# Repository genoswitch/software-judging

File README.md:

# software
toehold switch software

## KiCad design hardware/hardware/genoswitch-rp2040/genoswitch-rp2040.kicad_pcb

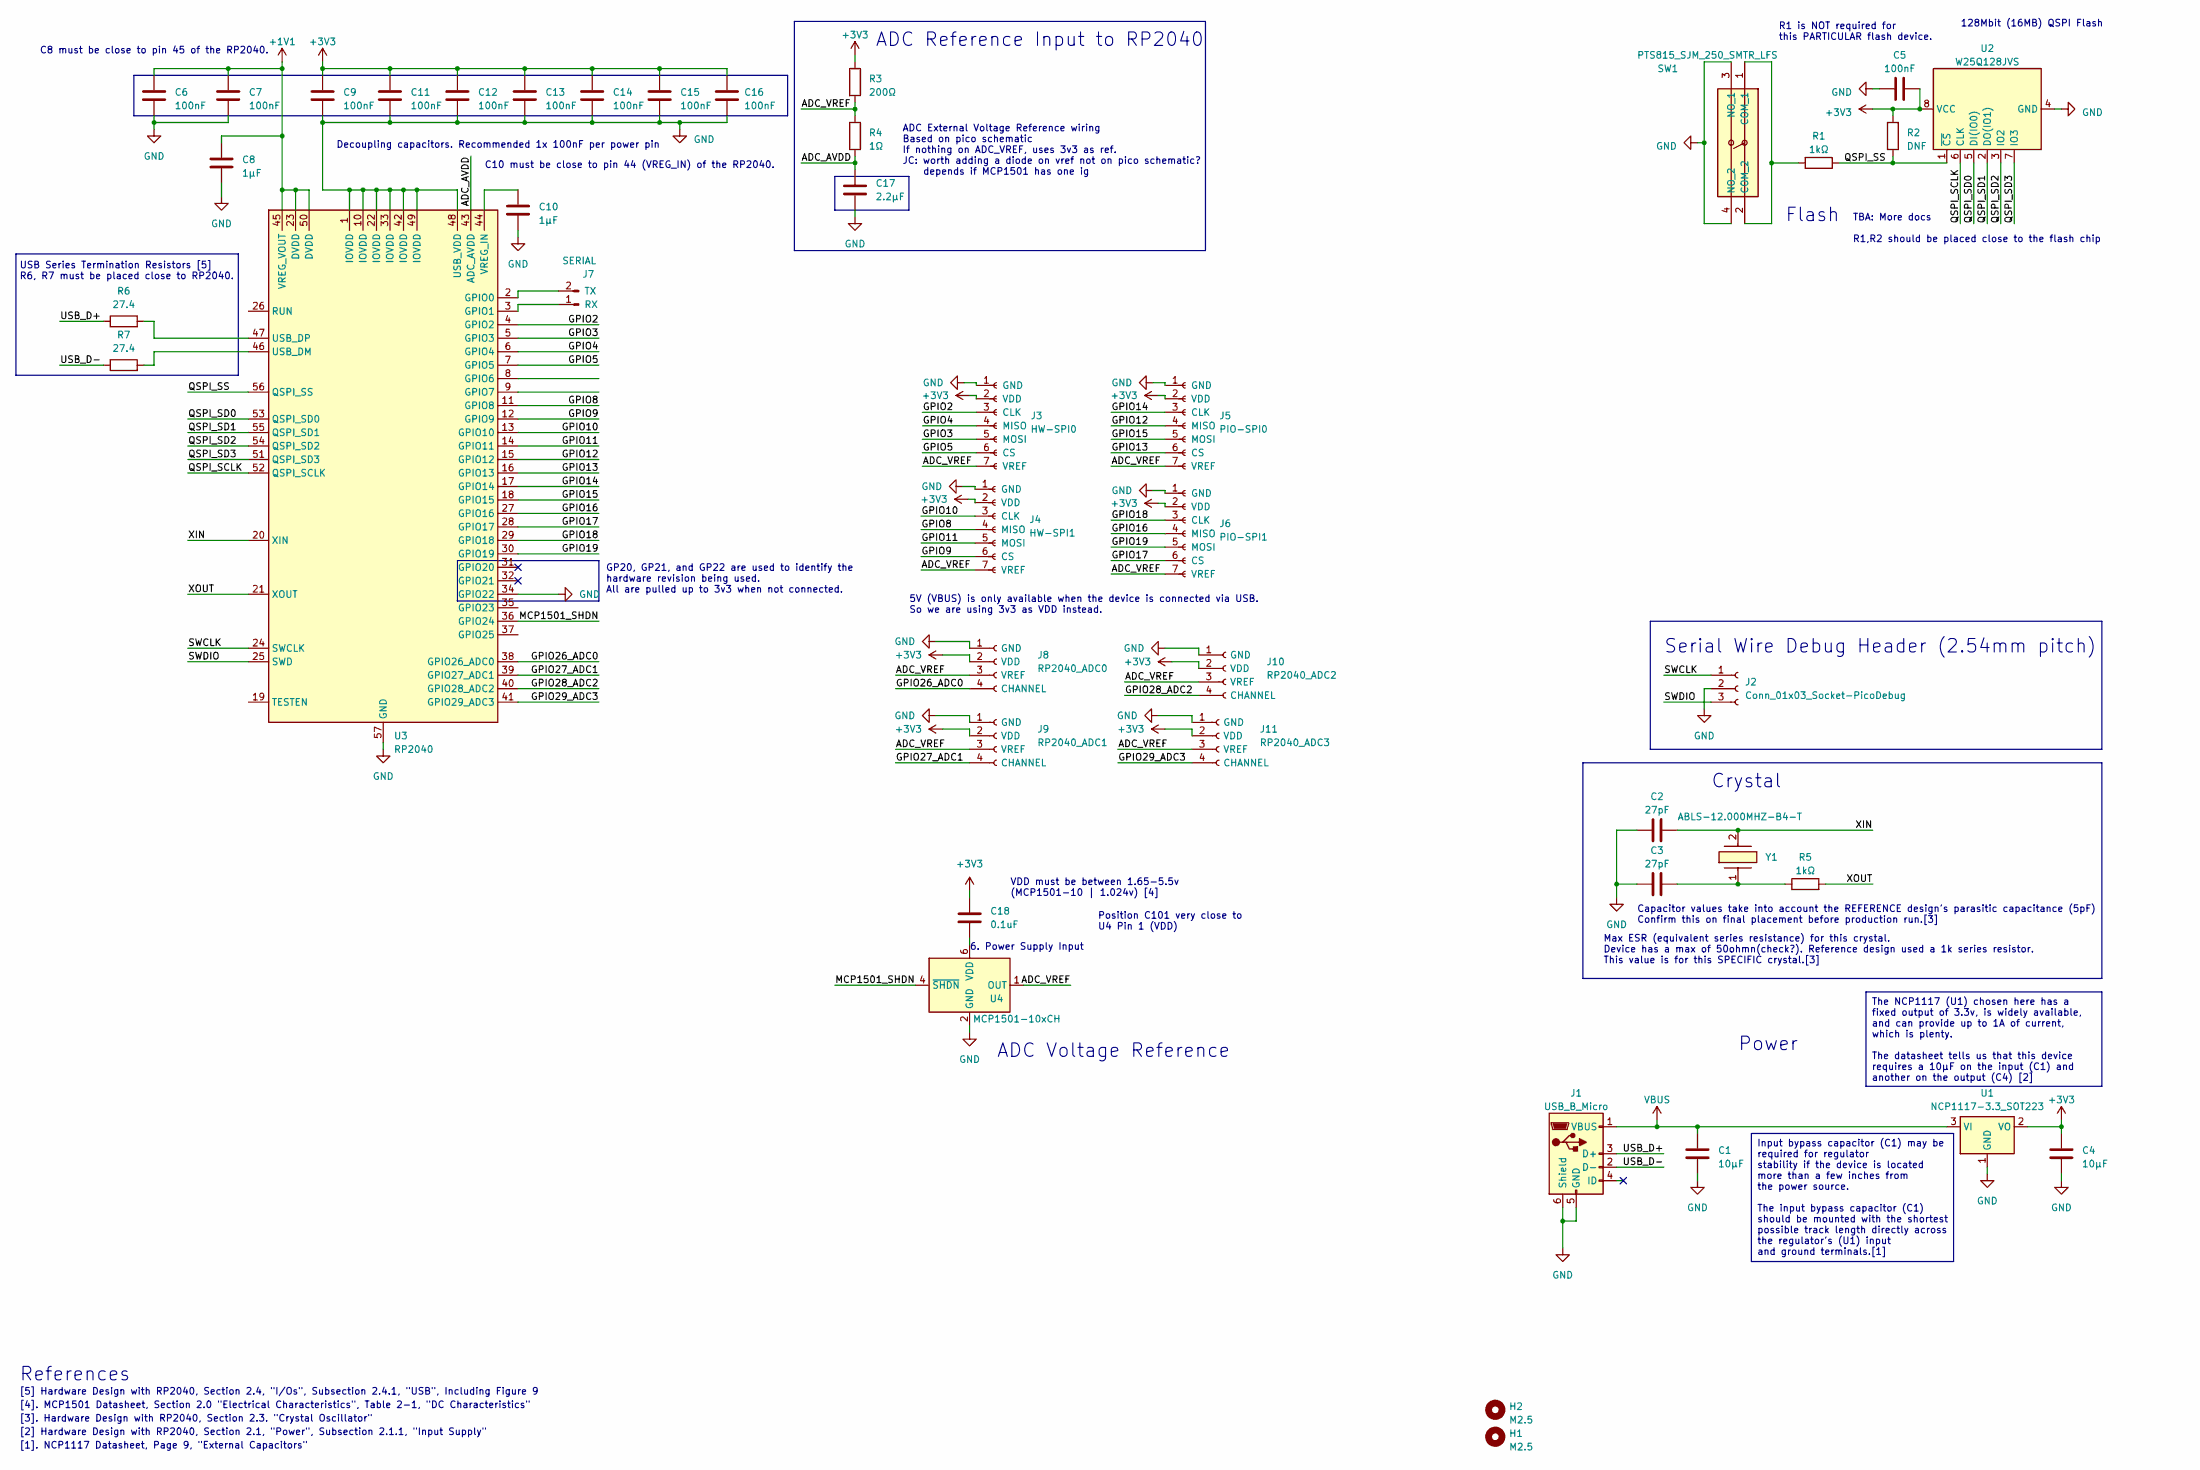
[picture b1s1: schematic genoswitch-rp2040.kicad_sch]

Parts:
C1, C4: 10μF; C_0201_0603Metric
C2, C3: 27pF; C_0201_0603Metric
C5, C6, C7, C9, C11, C12, C13, C14, C15, C16: 100nF; C_0201_0603Metric
C8, C10: 1μF; C_0201_0603Metric
C17: 2.2μF; C_0201_0603Metric
C18: 0.1uF; C_0201_0603Metric
H1, H2: M2.5; MountingHole_2.7mm_M2.5_Pad_TopBottom
J1: USB_B_Micro; USB_Micro-B_Amphenol_10118193-0001LF_Horizontal
J2: Conn_01x03_Socket-PicoDebug; PinHeader_1x03_P2.54mm_Vertical
J3: HW-SPI0; JST_PH_S7B-PH-K_1x07_P2.00mm_Horizontal
J4: HW-SPI1; JST_PH_S7B-PH-K_1x07_P2.00mm_Horizontal
J5: PIO-SPI0; JST_PH_S7B-PH-K_1x07_P2.00mm_Horizontal
J6: PIO-SPI1; JST_PH_S7B-PH-K_1x07_P2.00mm_Horizontal
J7: SERIAL; PinHeader_1x02_P2.54mm_Vertical
J8: RP2040_ADC0; JST_PH_S4B-PH-K_1x04_P2.00mm_Horizontal
J9: RP2040_ADC1; JST_PH_S4B-PH-K_1x04_P2.00mm_Horizontal
J10: RP2040_ADC2; JST_PH_S4B-PH-K_1x04_P2.00mm_Horizontal
J11: RP2040_ADC3; JST_PH_S4B-PH-K_1x04_P2.00mm_Horizontal
R1, R5: 1kΩ; R_0201_0603Metric
R2: DNF; R_0201_0603Metric
R3: 200Ω; R_0201_0603Metric
R4: 1Ω; R_0201_0603Metric
R6, R7: 27.4; R_0201_0603Metric
SW1: PTS815_SJM_250_SMTR_LFS; PTS815SJM250SMTRLFS; Mouser Part Number 611-PTS815SJM250SMTR
U1: NCP1117-3.3_SOT223; SOT-223-3_TabPin2
U2: W25Q128JVS; SOIC-8_5.23x5.23mm_P1.27mm
U3: RP2040; QFN-56-1EP_7x7mm_P0.4mm_EP3.2x3.2mm
U4: MCP1501-10xCH; SOT-23-6
Y1: ABLS-12.000MHZ-B4-T; ABLS; Mouser Part Number 815-ABLS-12.0M-T

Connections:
+1V1: C6.1, C7.1, C8.1, U3.23 (DVDD), U3.45 (VREG_VOUT), U3.50 (DVDD)
+3V3: C4.1, C5.2, C9.1, C11.1, C12.1, C13.1, C14.1, C15.1, C16.1, C18.2, J3.2 (VDD), J4.2 (VDD), J5.2 (VDD), J6.2 (VDD), J8.2 (VDD), J9.2 (VDD), J10.2 (VDD), J11.2 (VDD), R2.2, R3.1, U1.2 (VO), U2.8 (VCC)
/ADC_AVDD: C17.1, R4.2, U3.43 (ADC_AVDD)
/ADC_VREF: J3.7 (VREF), J4.7 (VREF), J5.7 (VREF), J6.7 (VREF), J8.3 (VREF), J9.3 (VREF), J10.3 (VREF), J11.3 (VREF), R3.2, R4.1, U4.1 (OUT)
/GPIO4: J3.4 (DOUT), U3.6 (GPIO4)
/GPIO5: J3.6 (CS), U3.7 (GPIO5)
/GPIO6: J3.3 (CLK), U3.4 (GPIO2), U3.8 (GPIO6)
/GPIO7: J3.5 (DIN), U3.5 (GPIO3), U3.9 (GPIO7)
/GPIO8: J4.4 (DOUT), U3.11 (GPIO8)
/GPIO9: J4.6 (CS), U3.12 (GPIO9)
/GPIO10: J4.3 (CLK), U3.13 (GPIO10)
/GPIO11: J4.5 (DIN), U3.14 (GPIO11)
/GPIO12: J5.4 (DOUT), U3.15 (GPIO12)
/GPIO13: J5.6 (CS), U3.16 (GPIO13)
/GPIO14: J5.3 (CLK), U3.17 (GPIO14)
/GPIO15: J5.5 (DIN), U3.18 (GPIO15)
/GPIO16: J6.4 (DOUT), U3.27 (GPIO16)
/GPIO17: J6.6 (CS), U3.28 (GPIO17)
/GPIO18: J6.3 (CLK), U3.29 (GPIO18)
/GPIO19: J6.5 (DIN), U3.30 (GPIO19)
/GPIO26_ADC0: J8.4 (CHANNEL), U3.38 (GPIO26_ADC0)
/GPIO27_ADC1: J9.4 (CHANNEL), U3.39 (GPIO27_ADC1)
/GPIO28_ADC2: J10.4 (CHANNEL), U3.40 (GPIO28_ADC2)
/GPIO29_ADC3: J11.4 (CHANNEL), U3.41 (GPIO29_ADC3)
/MCP1501_SHDN: U3.36 (GPIO24), U4.4 (~SHDN)
/QSPI_SCLK: U2.6 (CLK), U3.52 (QSPI_SCLK)
/QSPI_SD0: U2.5 (DI(IO0)), U3.53 (QSPI_SD0)
/QSPI_SD1: U2.2 (DO(IO1)), U3.55 (QSPI_SD1)
/QSPI_SD2: U2.3 (IO2), U3.54 (QSPI_SD2)
/QSPI_SD3: U2.7 (IO3), U3.51 (QSPI_SD3)
/QSPI_SS: R1.1, R2.1, U2.1 (~CS), U3.56 (QSPI_SS)
/SWCLK: J2.1, U3.24 (SWCLK)
/SWDIO: J2.3, U3.25 (SWD)
/USB_D+: J1.3 (D+), R6.1
/USB_D-: J1.2 (D-), R7.1
/XIN: C2.2, U3.20 (XIN), Y1.2
/XOUT: R5.2, U3.21 (XOUT)
GND: C1.2, C2.1, C3.1, C4.2, C5.1, C6.2, C7.2, C8.2, C9.2, C10.2, C11.2, C12.2, C13.2, C14.2, C15.2, C16.2, C17.2, J1.5 (GND), J1.6 (Shield), J2.2, J3.1 (GND), J4.1 (GND), J5.1 (GND), J6.1 (GND), J8.1 (GND), J9.1 (GND), J10.1 (GND), J11.1 (GND), SW1.3 (NO_1), SW1.4 (NO_2), U1.1 (GND), U2.4 (GND), U3.1 (IOVDD), U3.10 (IOVDD), U3.22 (IOVDD), U3.33 (IOVDD), U3.34 (GPIO22), U3.42 (IOVDD), U3.48 (USB_VDD), U3.49 (IOVDD), U3.57 (GND), U4.2 (GND), U4.3 (GND), U4.5 (GND)
unnamed: C3.2, R5.1, Y1.1
unnamed: J7.1 (RX), U3.3 (GPIO1)
unnamed: J7.2 (TX), U3.2 (GPIO0)
unnamed: R1.2, SW1.1 (COM_1), SW1.2 (COM_2)
unnamed: R7.2, U3.46 (USB_DM)
unnamed: R6.2, U3.47 (USB_DP)
unnamed: C10.1, U3.44 (VREG_IN)
unnamed: C18.1, U4.6 (VDD)
VBUS: C1.1, J1.1 (VBUS), U1.3 (VI)

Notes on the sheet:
The NCP1117 (U1) chosen here has a fixed output of 3.3v, is widely available, and can provide up to 1A of current, which is plenty. The datasheet tells us that this device requires a 10μF on the input (C1) and another on the output (C4) [2]
Input bypass capacitor (C1) may be required for regulator stability if the device is located more than a few inches from the power source. The input bypass capacitor (C1) should be mounted with the shortest possible track length directly across the regulator's (U1) input and ground terminals.[1]
VDD must be between 1.65-5.5v (MCP1501-10 | 1.024v) [4]
6. Power Supply Input
5V (VBUS) is only available when the device is connected via USB. So we are using 3v3 as VDD instead.
[4]. MCP1501 Datasheet, Section 2.0 "Electrical Characteristics", Table 2-1, "DC Characteristics"
Position C101 very close to U4 Pin 1 (VDD)
[5] Hardware Design with RP2040, Section 2.4, "I/Os", Subsection 2.4.1, "USB", Including Figure 9
128Mbit (16MB) QSPI Flash
USB Series Termination Resistors [5] R6, R7 must be placed close to RP2040.
[3]. Hardware Design with RP2040, Section 2.3. "Crystal Oscillator"
Decoupling capacitors. Recommended 1x 100nF per power pin
GP20, GP21, and GP22 are used to identify the hardware revision being used. All are pulled up to 3v3 when not connected.
Power
Serial Wire Debug Header (2.54mm pitch)
Crystal
R1 is NOT required for this PARTICULAR flash device.
[1]. NCP1117 Datasheet, Page 9, "External Capacitors"
ADC Voltage Reference
C10 must be close to pin 44 (VREG_IN) of the RP2040.
ADC External Voltage Reference wiring Based on pico schematic If nothing on ADC_VREF, uses 3v3 as ref. JC: worth adding a diode on vref not on pico schematic? depends if MCP1501 has one ig
TBA: More docs R1,R2 should be placed close to the flash chip
C8 must be close to pin 45 of the RP2040.
ADC Reference Input to RP2040
Capacitor values take into account the REFERENCE design's parasitic capacitance (5pF) Confirm this on final placement before production run.[3]
Max ESR (equivalent series resistance) for this crystal. Device has a max of 50ohmn(check?). Reference design used a 1k series resistor. This value is for this SPECIFIC crystal.[3]
Flash
[2] Hardware Design with RP2040, Section 2.1, "Power", Subsection 2.1.1, "Input Supply"
References

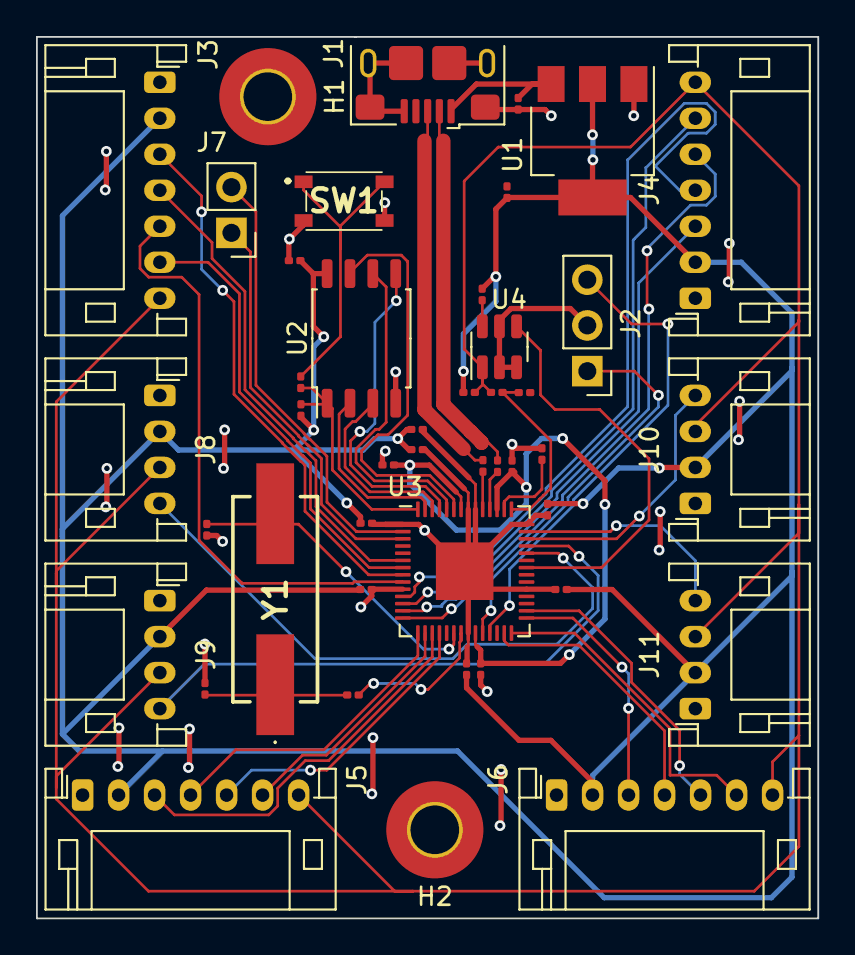
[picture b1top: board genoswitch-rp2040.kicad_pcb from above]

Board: 2 copper layers, 43.4 x 49.0 mm, 44 parts (0 on the bottom side), 47 nets.

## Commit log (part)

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2023-01-25 (lib) Add pico-sdk submodule
2023-01-25 add build/ folders to gitignore
2023-01-25 Fetch FreeRTOS import script from kernel repo
2023-01-28 (ide): Set CMake build and src directories
2023-01-28 (ide): Add picoprobe debug configuration
2023-01-28 Include FreeRTOS (and config dir); link Kernel and Kernel-Heap4
2023-01-28 Add comments, move prototypes to .h file
2023-01-28 Add cortex debug files, comments to gitignore
2023-01-28 Add tinyusb config files from webusb_serial demo (unmodified)
2023-01-29 Initial TinyUSB WebUSB support (enumerates successfully)
    Code based on the TinyUSB WebUSB_Serial demo, but we are still using FreeRTOS.
    FreeRTOS code inspired from cdc freertos examples from TinyUSB.
2023-02-17 Add cmake-git-version-tracking submodule
2023-02-18 Display hw/fw information over stdout on boot
2023-03-11 PoC queue based messaging between tasks
2023-03-12 (tasks/mcu_temp): Send temp data over usb, optionally over stdout configurable by #define
2023-03-23 (cmake): Move main cmake calls to own file
    This is so that we can split the flashloader and main program into different cmake files.
2023-03-23 (cmake): Add module path var and linker script helper
2023-03-23 (cmake/main): Create subproject name var
2023-03-23 (cmake): Set project variable
2023-03-23 (cmake): Include new cmake scripts in build
2023-03-24 (cmake): Update linker helper for new linker files
2023-03-24 (cmake): PoC new way of combining binaries
    This method is based off of picowota (https://github.com/usedbytes/picowota) as well as the pico sdk itself.
    With this method we can create all of the expected output files (.elf, .hex, .uf2) as well as register it as an executable in cmake.
    This commit is just a proof of concept, in later commits this will be extended to have the functionality described above.
2023-03-25 (linker): pico-flashloader requires application to have boot2
    Unlike picowota, pico-flashloader uses boot2 to identify the start of image. If space is a concern we could change this behaviour to use a magic string like picowota instead.
2023-04-06 (cmake/flashloader): Only make bin output
2023-04-06 (cmake/combined): Generate a combined uf2
2023-04-06 (combined/cmake): Add comments for custom commands
2023-04-09 (linker): Move flashloader ld files to own dir
2023-04-09 (linker): Add flashloader dir to linker include
2023-04-09 (core): Convert to static library
2023-04-09 (cmake) Move flashloader files to own dir
2023-04-09 (cmake/root): Fix paths for flashloader components
2023-04-09 Add INCLUDES_FLASHLOADER preprocessor macro
2023-04-09 (lib): Update pico-sdk to release v1.5.0
2023-04-09 (core/vendor_request): Add missing semicolon
2023-04-11 (flashloader): Create DMA standard crc32 func
2023-04-11 (core/tinyusb-config): Add #define scoped changes for DFU class
2023-04-11 (core/tusb-conf): Add breakdown and defines for microsoft os 2.0 descriptor component sizes
    I plan to swap from using either fixed (such as `U16_TO_U8S_LE(0x000A)`) or dynamic (full size - element - element) to using defines to allow me to more easily add additional components for additiona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
2023-04-11 (core/tusb-conf): Replace dynamic total lengths with defines
2023-04-11 (core/tusb-conf): Replace registry property dynamic length with define
2023-04-12 (lib): Update tinyusb to upstream HEAD
    As of the time of writing, there are about 300 commits between the latest release (0.15.0, and HEAD) It seems that the previous issue that arised in 58bfc1718faabb2aa632266ceec93ae5667e5a8f has since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
2023-05-06 Make bulk message structs static
    Avoids linker multiple defines errors in CI/CD
2023-05-06 (ci): Switch to a matrix, upload artifacts to github pages
2023-05-06 (ci): Pass CMAKE_BUILD_TYPE to cmake configure
    This allows cmake to respect the build-type.
    Prior to this commit, all build types were being build as Release, with CMake noting that build type was not set
2023-05-13 Add flash binary end vendor custom request
2023-05-13 Add initial power circuitry from minimal design example
2023-05-14 Add RP2040 using default package for now
    Note that the minimal example uses a different KiCad package
2023-05-14 (flashloader/util): Add crc32 func without reflection or final xor
2023-05-14 Add ringbuf submodule (fork)
2023-05-15 Parse intel hex records sent over DFU
2023-05-15 Rename flashloader/flashloader.[c|h] to flashloader/main.[c|h]
2023-05-15 (flashloader/ihex): Experiment with processing records like rhulme's demo does
2023-05-18 (symbols): Split out pins with the same function
    IOVDD, other have multiple pins. On the stock symbol they are combined into a single pin
2023-05-18 Switch to new custom rp2040 part
2023-05-18 Add 16MB QSPI chip
2023-05-19 Add crystal (reference design for now)
2023-06-04 zero out memory region for rec
2023-06-04 (flashloader/ihex/record): Use correct indexes to calc ulba
    nrf-intel-hex shows data[0] and data[1] but this is a subsection of the data starting at index 4, so index 4 and 5.
2023-06-04 (flashloader/ihex/record): Add getAddress function
2023-06-07 (flashloadr/ihex/process): Allow 96k for buffered firmware update
2023-06-07 (flashloader/combined): Create sectioned hex files.
    The stock .hex file contains two sections, the flashloader, starting at 0x10000000, and the application, currently starting at 0x10001000.
    At present only the application is updated when using the DFU mode, so we need a way to only write the application to the flash.
    We could hardcode offsets in the firmware but that would make it difficult when the offset is changed.
    Instead, we are making seperate .hex files for each of the two sections.
    We can then use micro:bit's universal hex format to merge them together in a way where we can clearly identify when each section starts without relying on fixed addresses.
2023-06-07 (flashloader/cmake): Add command to create universal hex file
2023-06-07 (flashloader/ihex/record): Add section ID enums
2023-06-07 (flashloader/ihex/process): Parse custom data instead of ihex data records
2023-06-07 (tusb-config): Remove _ prefix from header guard
2023-06-07 (ci): Hold snapd
    When apt upgrading, if snap is unavailable the command will hang for up to 30 mins (see below)
    ```Preparing to unpack .../firefox_1%3a1snap1-0ubuntu2_amd64.deb ...
    => Installing the firefox snap
    ==> Checking connectivity with the snap store
    ===> Unable to contact the store, trying every minute for the next 30 minutes```
    This commit attempts to stop snap-depenent packages from installing.
2023-06-07 (flashloader/combined): Install deps for universal-hex
2023-06-07 Setup Team Name
2023-06-08 (flashloader/crc32): Don't make crc32 functions static
2023-06-08 (flashloader/ihex): move FLASH_IMAGE_OFFSET to header file, add record import
2023-06-09 (flashloader/crc32): Reduce code dupe, fix alternate crc32 calc for flashloader
2023-06-09 (flashloader/ihex/process): Call flashImage on EOF for now
    Technically the transfer is still in progress so this should be called from tud_dfu_manifest_cb instead but that requires some refactoring.
2023-06-09 (flashloader/ihex/flash): Enter critical mode if using more than one core
    Otherwise it will hang here
2023-06-09 (flashloader/ihex/process): Adjust comments, print debug statements
2023-06-10 (rtos/config): Use a single core for now as tasks are not yet thread-safe
2023-06-10 (FreeRTOS): (Re-)enable dual cores, multiple priorities and core affinity
2023-06-10 (flashloader): Create spinlock initial tidied ver
2023-06-11 (ide/launch.json): Remove deprecated runToMain in favour of runToEntryPoint, lint file
2023-06-11 (flashloader/cmake): unset node and npm vars on each run
2023-06-11 Increase schematic size to A3 (was A4)
2023-06-11 Add OHW license, note to readme
2023-06-11 Rename LICENSE.md to LICENSE
2023-06-11 (ci): Add mirror to iGEM GitLab
2023-06-12 (ci/mirror): Update action comit
2023-06-13 Add M2.5 mounting holes (same as Pi Pico)
2023-06-14 (squash): Initial merging CI action
    commit 4011342ece50584bfff10b96bbbcc4b7fdb8c4a1
    Author: James Cahill <jcahill773@gmail.com>
    Date: Wed Jun 14 10:59:29 2023 +0100
    (ci/merge): Cross reference commit on GitHub
    commit 796af9a05444234b099d44ea476214dba0fccf6f
    Author: James Cahill <jcahill773@gmail.com>
2023-06-14 (ci/mirror): Add merge webhook trigger job
2023-06-14 (ci/merge): Correct namespace for payload content
2023-06-14 (ci/merge): Fix if syntax
2023-06-14 (ci/mirror): Add merge job
2023-06-17 (ci/merge): Reconstruct .gitmodules in CI job
    To correct submodules in folders (where .gitmodules is not in the root dir)
2023-06-19 (README): Add initial installation docs
2023-06-19 (readme): Add note about debug packages for arch
2023-06-29 (ci/workflows/merge): Attempt to unify repository_dispatch jobs
2023-07-10 (lib): Update pico-sdk to version 1.5.1
2023-07-16 note that regulator is U1
2023-07-17 Add HW SPI MCP3008s
2023-07-17 Add PIO SPI MCP3008s
2023-07-18 Add 0201/0603M footprints for resistors, capacitors
2023-07-18 Add footprint for C2, C3
2023-07-18 (ci/github): Switch to new mirror action
2023-08-05 (tinyusb-config/usb_descriptors): Don't advertise support for manifestation tolerance as it is not supported yet
2023-08-05 (flashloader): Call flashImage in tud_dfu_manifest_cb
2023-08-05 Fix reconstruct-root-gitmodules for new paths
2023-08-05 (ci/github/mirror): Add path variable
2023-08-07 Remove MCP3008s from main PCB, add connectors instead
2023-08-08 Add ability to determine device type using 3 GPIOs
2023-08-08 Change 0603 components to 0402 sizes
2023-08-08 Initial partial layout
2023-08-08 Swap to horizonal JST PH connector
2023-08-09 Set differantial pair gap, width for USB data, add netclasses to 3v3, USB_D*
2023-08-09 Add +1v1, VBUS, GND to Power netclass
2023-08-11 Route U2, SW1 -> RP2040
2023-08-11 (ADC_CONN): Make GND pin 1
2023-08-11 Add ADC Channel sockets x4, place on board 5mil apart
2023-08-11 Update PCB from schematic for new 0602 sizing
2023-08-11 Add missing decoupling cap for 7th power pin, renumber C16->C17, C101->C18
2023-08-11 (schematic): Add R6, R7 series termination resistors
    TODO: document in schematic
2023-08-11 Initial routing of C6, C15, C16, R6, R7
2023-08-11 Place capacitor C4, move U1 text
2023-08-11 Snake +3v3 across the board
2023-08-11 Route TX,RX pin header
2023-08-11 Route J4,J5,J6
2023-08-11 Place Y1 next to RP2040, route traces around it
2023-08-11 misc drc fixes (empty traces)
2023-08-11 Update via sizes
2023-08-11 Commit .kicad_pro file for 7dc94fe898b3e63f5aeb923815829955d28dfb08
2023-08-11 Re-trace board outline rails to adhere to new DRC rules
2023-08-11 added stuff
2023-08-12 Shift J5, J6 by 90 degrees to make board slightly smaller
2023-08-12 Route 1v1 rail, 3v3 links between U1 outputs
2023-08-12 Adjust positioning of +3v3 rail near U2
2023-08-13 Add ground fill, ground C6-C16
2023-08-13 Fix thermal relief on J2 GND
2023-08-13 Remove unncessary trace
2023-08-13 Adjust routing of +3V3 rail
2023-08-13 Add open-source-hardware svg asset
2023-08-17 Add initial kibot CI job using default kibot config yml
2023-08-17 (ci/github/kibot): Update schematic paths; job name
2023-08-17 (ci/github/commitMsg): Use DST_PATH in parentheses
2023-08-17 Remove old generated folders to prep for new method
2023-08-21 added a buch of stuff: all the pages miRBase integration nupack image requesting
2023-08-24 (frontend): Polyfill buffer
2023-08-24 (frontend/components): Use webp image format for static images
2023-08-24 (ci/github/merge): Uncomment source remote; adjust comments/step names
2023-08-24 (ci/github): Make commit-message-env.sh executable
2023-08-24 (ci/github/merge): Add merge-lfs job
2023-08-25 just commiting this so that there's an up to date version to pull from my laptop
2023-08-25 made reversal checkboxes work for main input page, added checkboxes to miRBase page
2023-08-28 (rp2040): Make screw hioles conductive on both layers
2023-09-17 added a bunch of stuff, miRBase integration, .fasta file integration
2023-10-01 PoC SPI communication using PIO
2023-10-01 Standardize header guards
2023-10-01 Update pinouts for GS connectors -> SPI
2023-10-01 Don't use hardcoded pin arrangements
2023-10-03 Matched colours of probability matrices to match colour scheme
2023-10-05 (core/mcp3008/pio): Attempt to set SPI clock speed
2023-10-07 Add AppImage building using GitHub Actions; remove unneeded files (#1)
    * Move files to src/
    * Initial make appimage script
    * (ci/github): Initial build script
    * Remove python venv dep
    * (make-appimage) set -e
    * (build): misc fixes
2023-10-07 (backend): Run npm install

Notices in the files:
hardware/hardware/genoswitch-rp2040/genoswitch-rp2040.kicad_pcb:
SPDX: CERN-OHL-W-2.0
